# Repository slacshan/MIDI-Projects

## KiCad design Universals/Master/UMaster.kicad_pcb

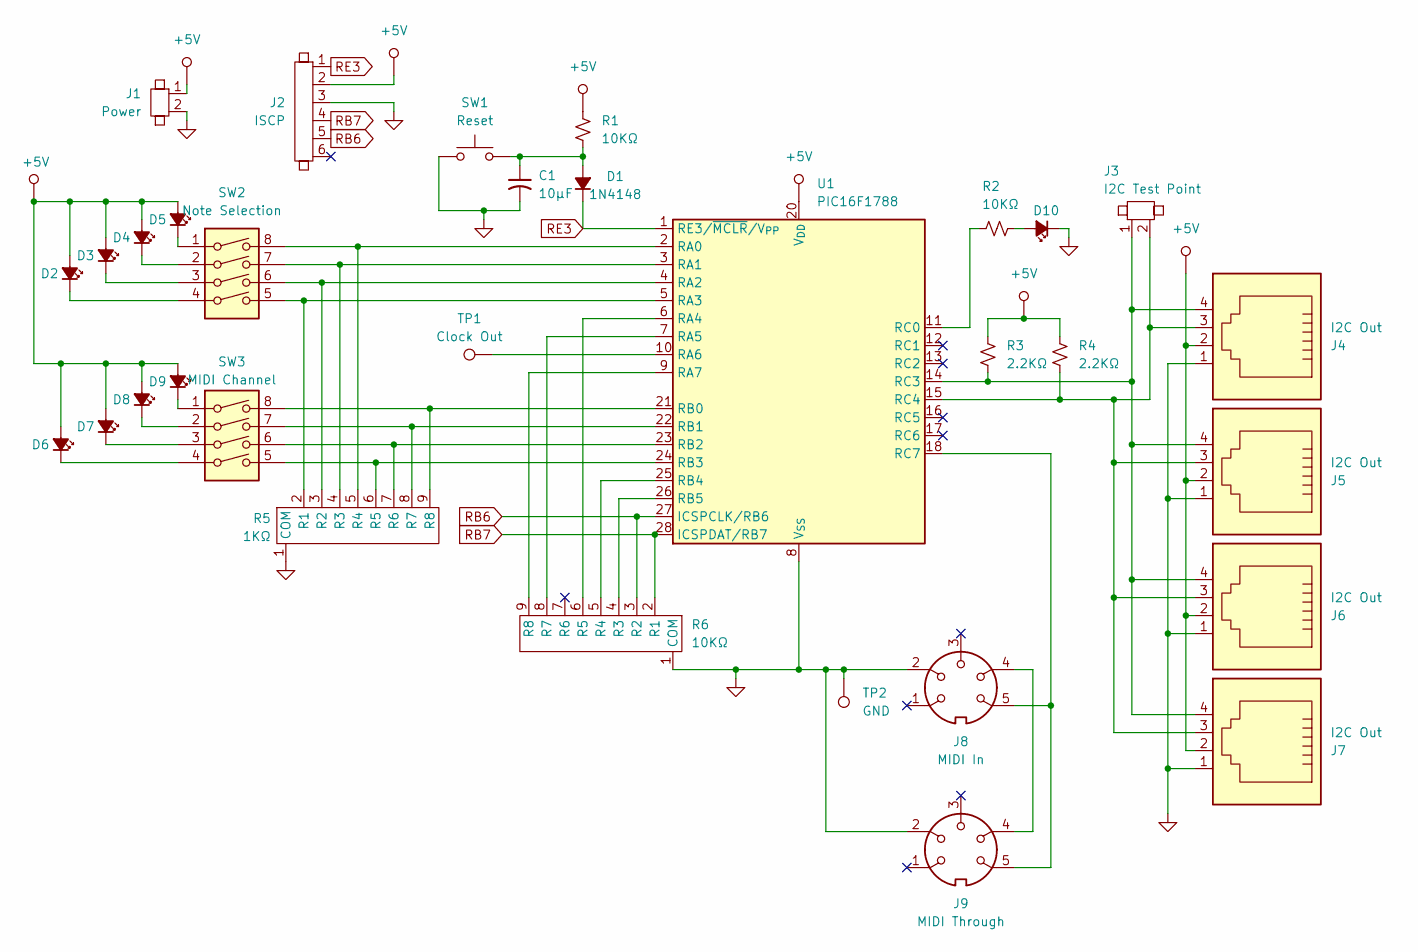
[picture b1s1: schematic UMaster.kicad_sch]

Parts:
C1: 10µF; C_Radial_D6.3mm_H11.0mm_P2.50mm
D1: 1N4148; D_0805
D2, D3, D4, D5, D6, D7, D8, D9, D10: LED_Small_Filled; D_0805
J1: Power; 2PinMolex
J2: ISCP; 1X6_100mil_Header
J3: I2C Test Point; 1X2_100mil_Header
J4, J5, J6, J7: I2C Out; RJ11
J8: MIDI In; DIN-5PIN_MIDI
J9: MIDI Through; DIN-5PIN_MIDI
R1, R2: 10KΩ; C_0805
R3, R4: 2.2KΩ; C_0805
R5: 1KΩ; 1x9_100mil_Header
R6: 10KΩ; 1x9_100mil_Header
SW1: Reset; SW_PUSH_6mm
SW2: Note Selection; DIP-8_W7.62mm
SW3: MIDI Channel; DIP-8_W7.62mm
TP1: Clock Out; 1X1_100mil_Header
TP2: GND; 1X1_100mil_Header
U1: PIC16F1788; QFN-28-1EP_6x6mm_P0.65mm_EP4.25x4.25mm

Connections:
GND: C1.2, D10.1 (K), J1.2, J2.3, J4.1, J5.1, J6.1, J7.1, J8.2, J9.2, R5.1 (COM), R6.1 (COM), SW1.1, TP2.1, U1.8 (V_{SS}), U1.19 (V_{SS})
unnamed: C1.1, D1.2 (A), R1.2, SW1.2
unnamed: D2.1 (K), SW2.4
unnamed: D3.1 (K), SW2.3
unnamed: D4.1 (K), SW2.2
unnamed: D5.1 (K), SW2.1
unnamed: D6.1 (K), SW3.4
unnamed: D7.1 (K), SW3.3
unnamed: D8.1 (K), SW3.2
unnamed: D9.1 (K), SW3.1
unnamed: D10.2 (A), R2.2
unnamed: J8.4, J9.4
unnamed: R5.2 (R1), SW2.5, U1.5 (RA3)
unnamed: R5.3 (R2), SW2.6, U1.4 (RA2)
unnamed: R5.4 (R3), SW2.7, U1.3 (RA1)
unnamed: R5.5 (R4), SW2.8, U1.2 (RA0)
unnamed: R5.6 (R5), SW3.5, U1.24 (RB3)
unnamed: R5.7 (R6), SW3.6, U1.23 (RB2)
unnamed: R5.8 (R7), SW3.7, U1.22 (RB1)
unnamed: R5.9 (R8), SW3.8, U1.21 (RB0)
unnamed: R6.4 (R3), U1.26 (RB5)
unnamed: R6.5 (R4), U1.25 (RB4)
unnamed: R6.6 (R5), U1.6 (RA4)
unnamed: R6.8 (R7), U1.7 (RA5)
unnamed: R6.9 (R8), U1.9 (RA7)
unnamed: TP1.1, U1.10 (RA6)
unnamed: R2.1, U1.11 (RC0)
unnamed: J3.1, J4.4, J5.4, J6.4, J7.4, R3.2, U1.14 (RC3)
unnamed: J3.2, J4.3, J5.3, J6.3, J7.3, R4.2, U1.15 (RC4)
unnamed: J8.5, J9.5, U1.18 (RC7)
RB6: J2.5, R6.3 (R2), U1.27 (ICSPCLK/RB6)
RB7: J2.4, R6.2 (R1), U1.28 (ICSPDAT/RB7)
RE3: D1.1 (K), J2.1, U1.1 (RE3/~MCLR/V_{PP})

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
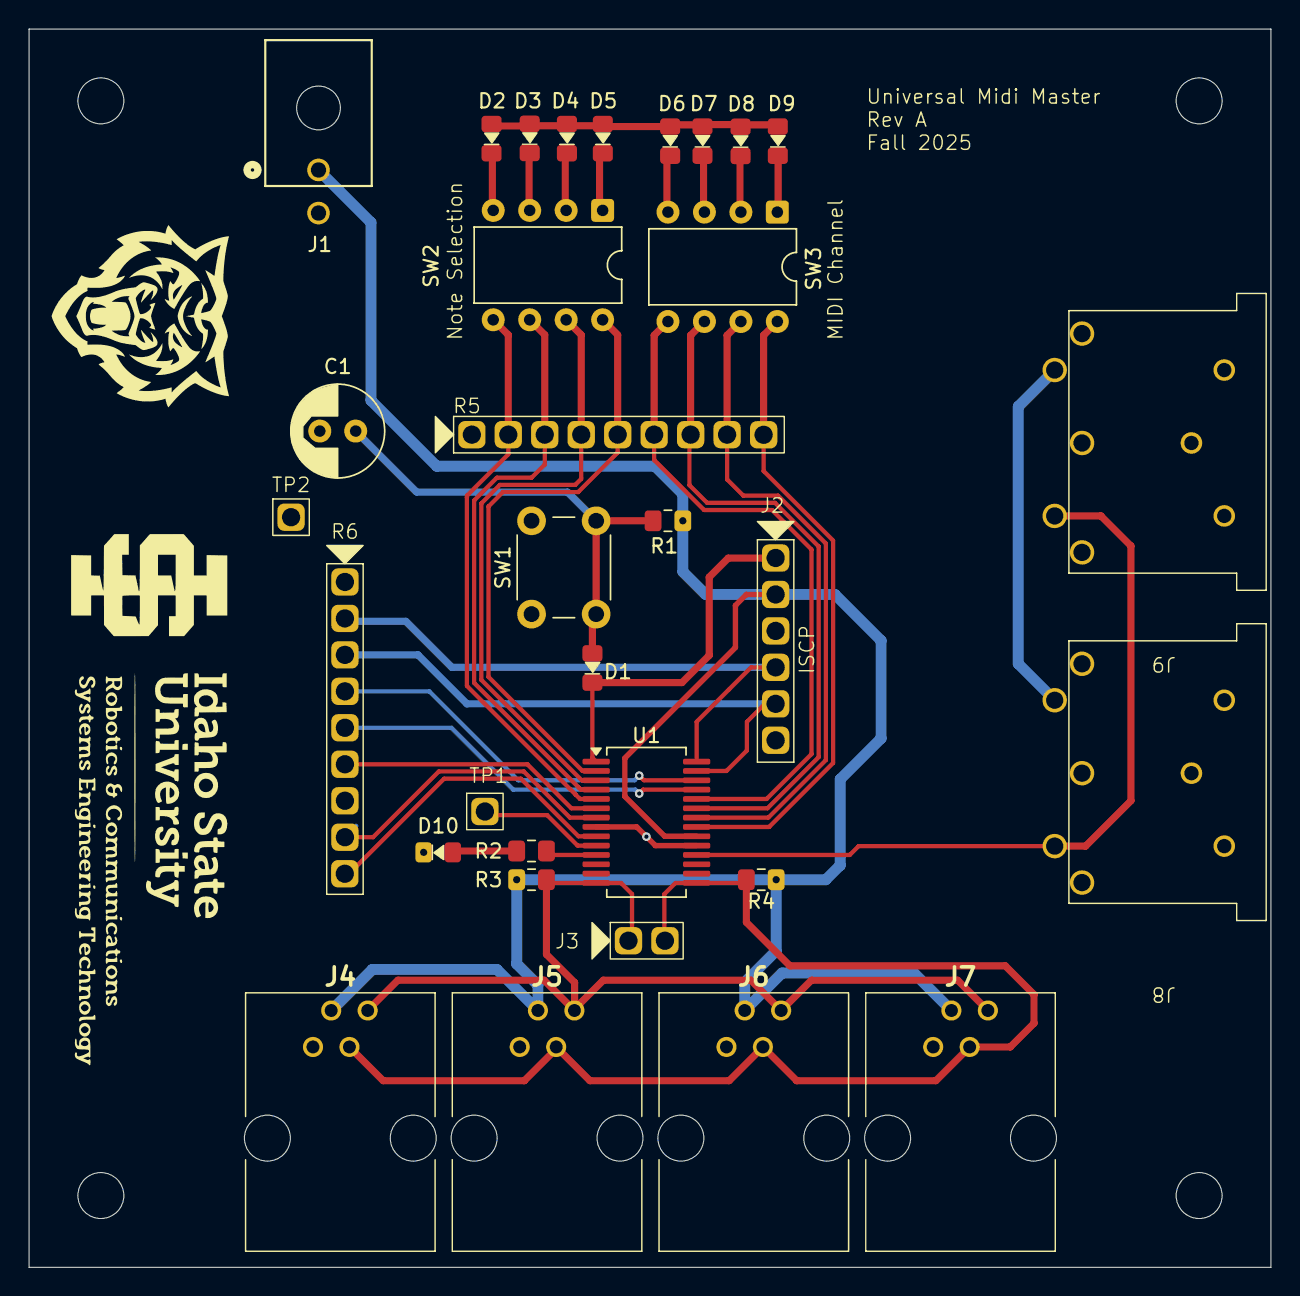
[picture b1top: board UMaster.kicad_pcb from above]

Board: 2 copper layers, 86.5 x 86.2 mm, 32 parts (0 on the bottom side), 35 nets.

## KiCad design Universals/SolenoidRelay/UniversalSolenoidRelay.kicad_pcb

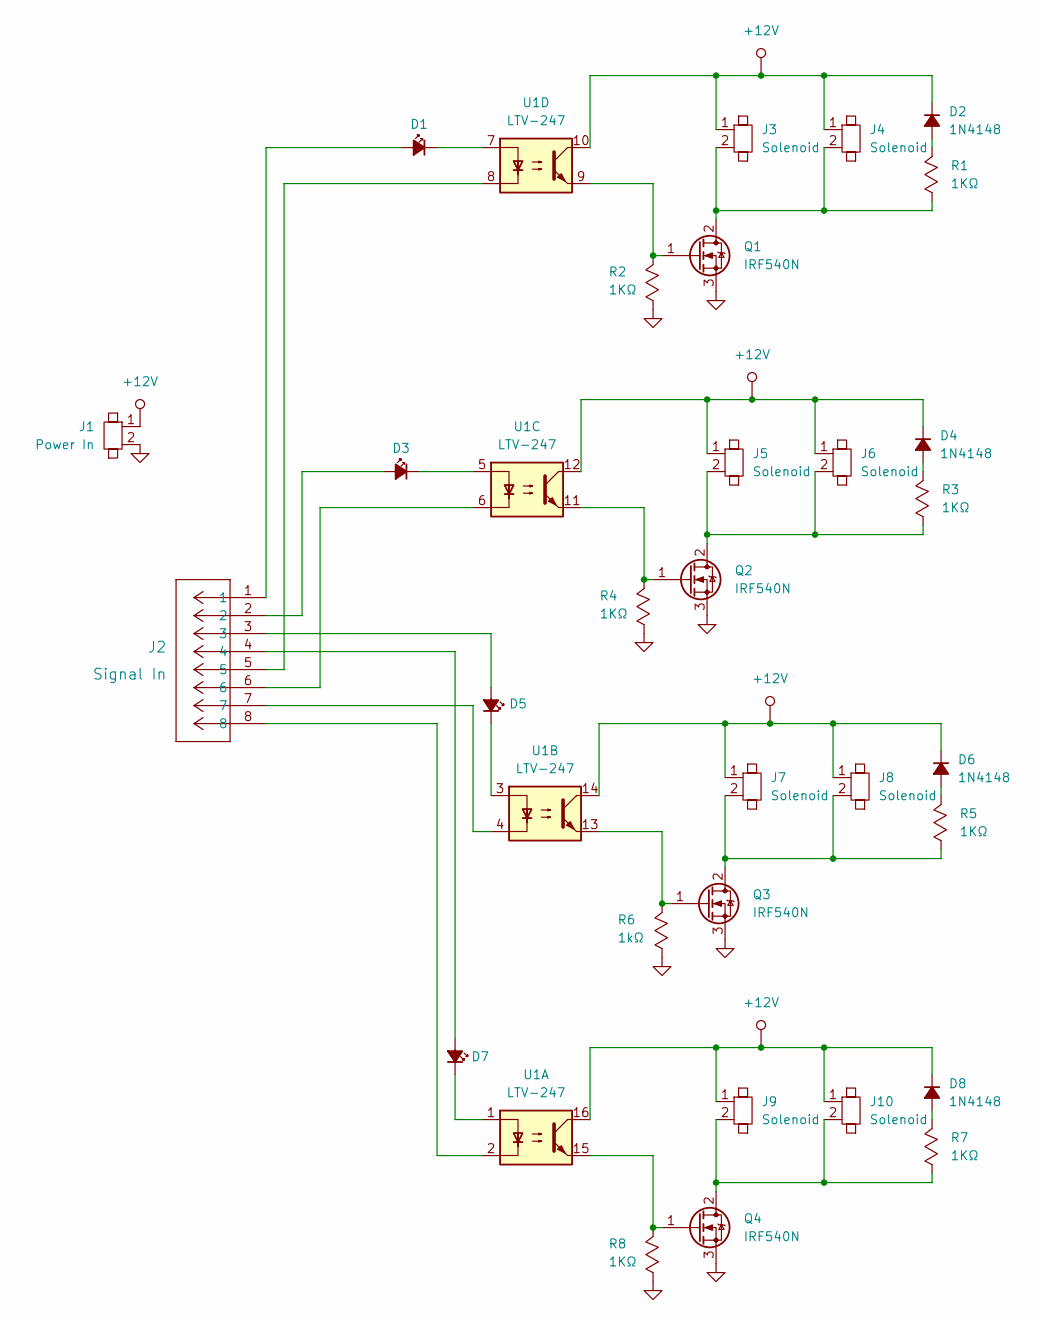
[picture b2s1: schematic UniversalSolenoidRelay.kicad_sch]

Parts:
D1, D3, D5, D7: LED; D_0805
D2, D4, D6, D8: 1N4148; D_0805
J1: Power In; 2PinMolex
J2: Signal In; 8PinMolex_3.00mmPitch
J3, J4, J5, J6, J7, J8, J9, J10: Solenoid; 2PinMolex
Q1, Q2, Q3, Q4: IRF540N; TO-220-3_Vertical
R1, R2, R3, R4, R5, R7, R8: 1KΩ; C_0805
R6: 1kΩ; C_0805
U1: LTV-247; SOP-16_4.4x10.4mm_P1.27mm

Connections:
GND: J1.2, Q1.3 (S), Q2.3 (S), Q3.3 (S), Q4.3 (S), R2.1, R4.1, R6.1, R8.1
unnamed: D1.2 (A), J2.1
unnamed: D1.1 (K), U1.7
unnamed: D2.2 (A), R1.2
unnamed: D3.2 (A), J2.2
unnamed: D3.1 (K), U1.5
unnamed: D4.2 (A), R3.2
unnamed: D5.2 (A), J2.3
unnamed: D5.1 (K), U1.3
unnamed: D6.2 (A), R5.2
unnamed: D7.2 (A), J2.4
unnamed: D7.1 (K), U1.1
unnamed: D8.2 (A), R7.2
unnamed: D2.1 (K), D4.1 (K), D6.1 (K), D8.1 (K), J1.1, J3.1, J4.1, J5.1, J6.1, J7.1, J8.1, J9.1, J10.1, U1.10, U1.12, U1.14, U1.16
unnamed: J2.5, U1.8
unnamed: J2.6, U1.6
unnamed: J2.7, U1.4
unnamed: J2.8, U1.2
unnamed: J3.2, J4.2, Q1.2 (D), R1.1
unnamed: Q1.1 (G), R2.2, U1.9
unnamed: J5.2, J6.2, Q2.2 (D), R3.1
unnamed: Q2.1 (G), R4.2, U1.11
unnamed: J7.2, J8.2, Q3.2 (D), R5.1
unnamed: Q3.1 (G), R6.2, U1.13
unnamed: J9.2, J10.2, Q4.2 (D), R7.1
unnamed: Q4.1 (G), R8.2, U1.15

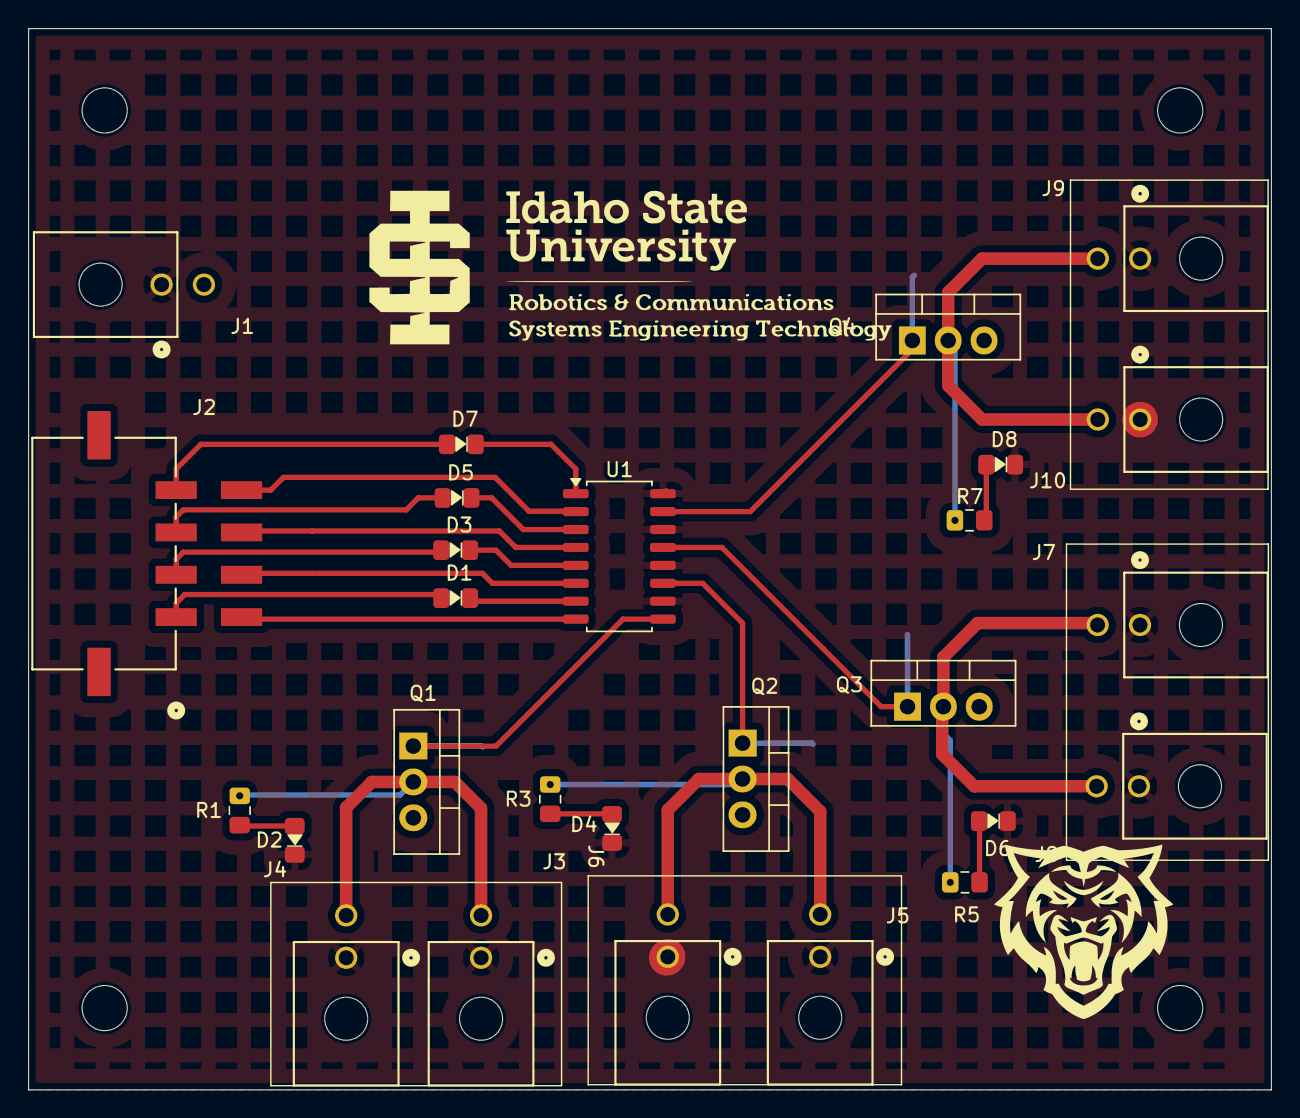
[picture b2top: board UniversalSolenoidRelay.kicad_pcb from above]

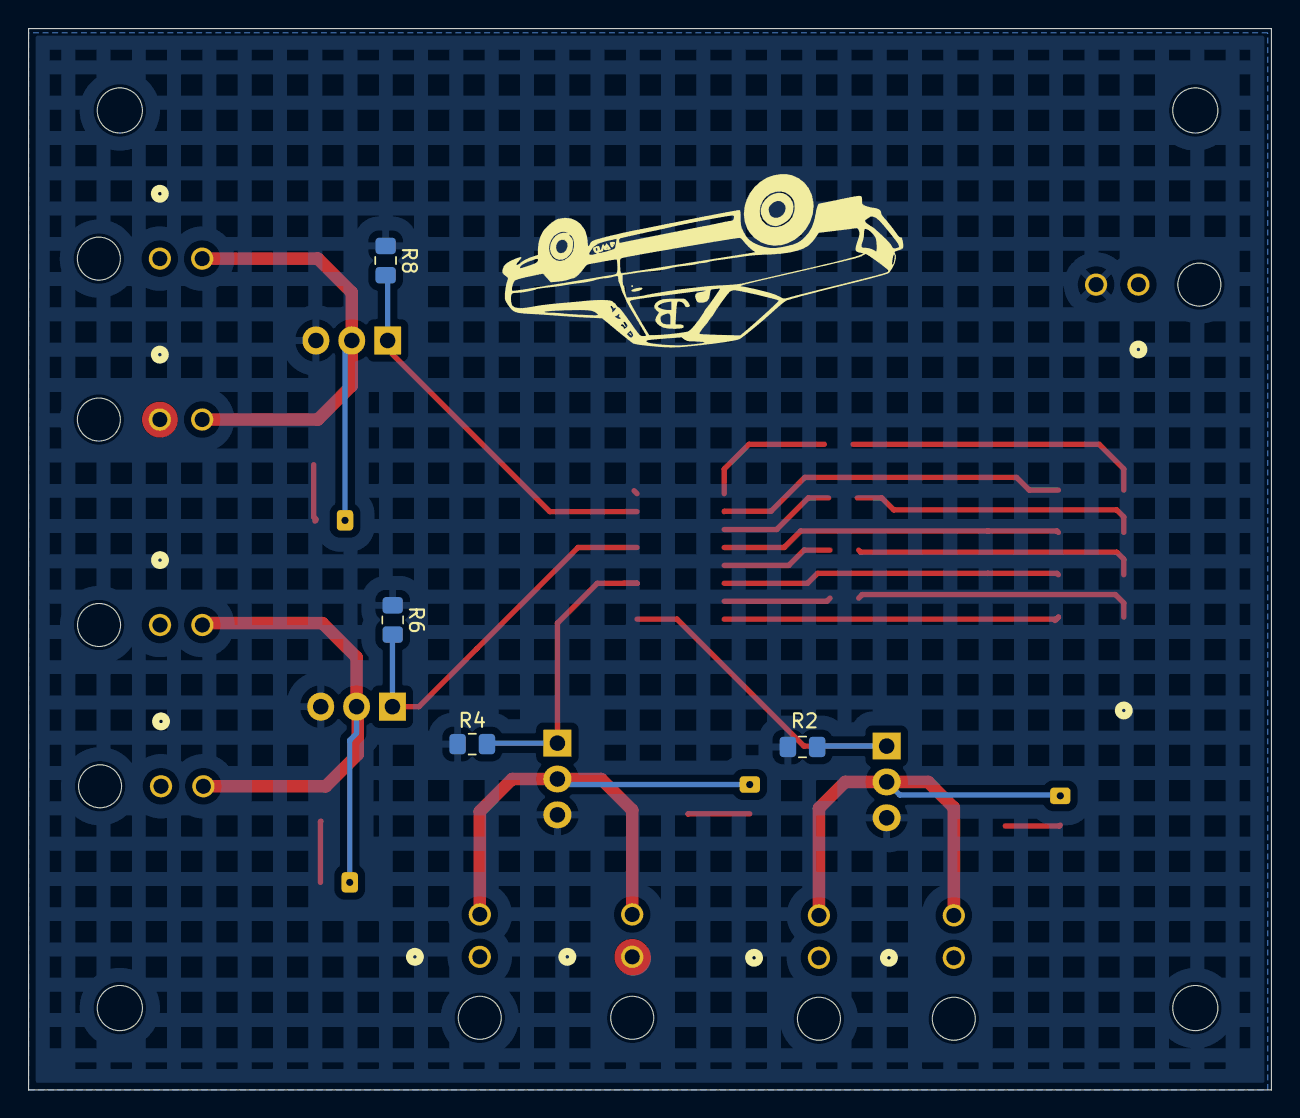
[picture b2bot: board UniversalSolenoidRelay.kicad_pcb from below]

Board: 2 copper layers, 88.1 x 75.2 mm, 31 parts (4 on the bottom side), 26 nets.

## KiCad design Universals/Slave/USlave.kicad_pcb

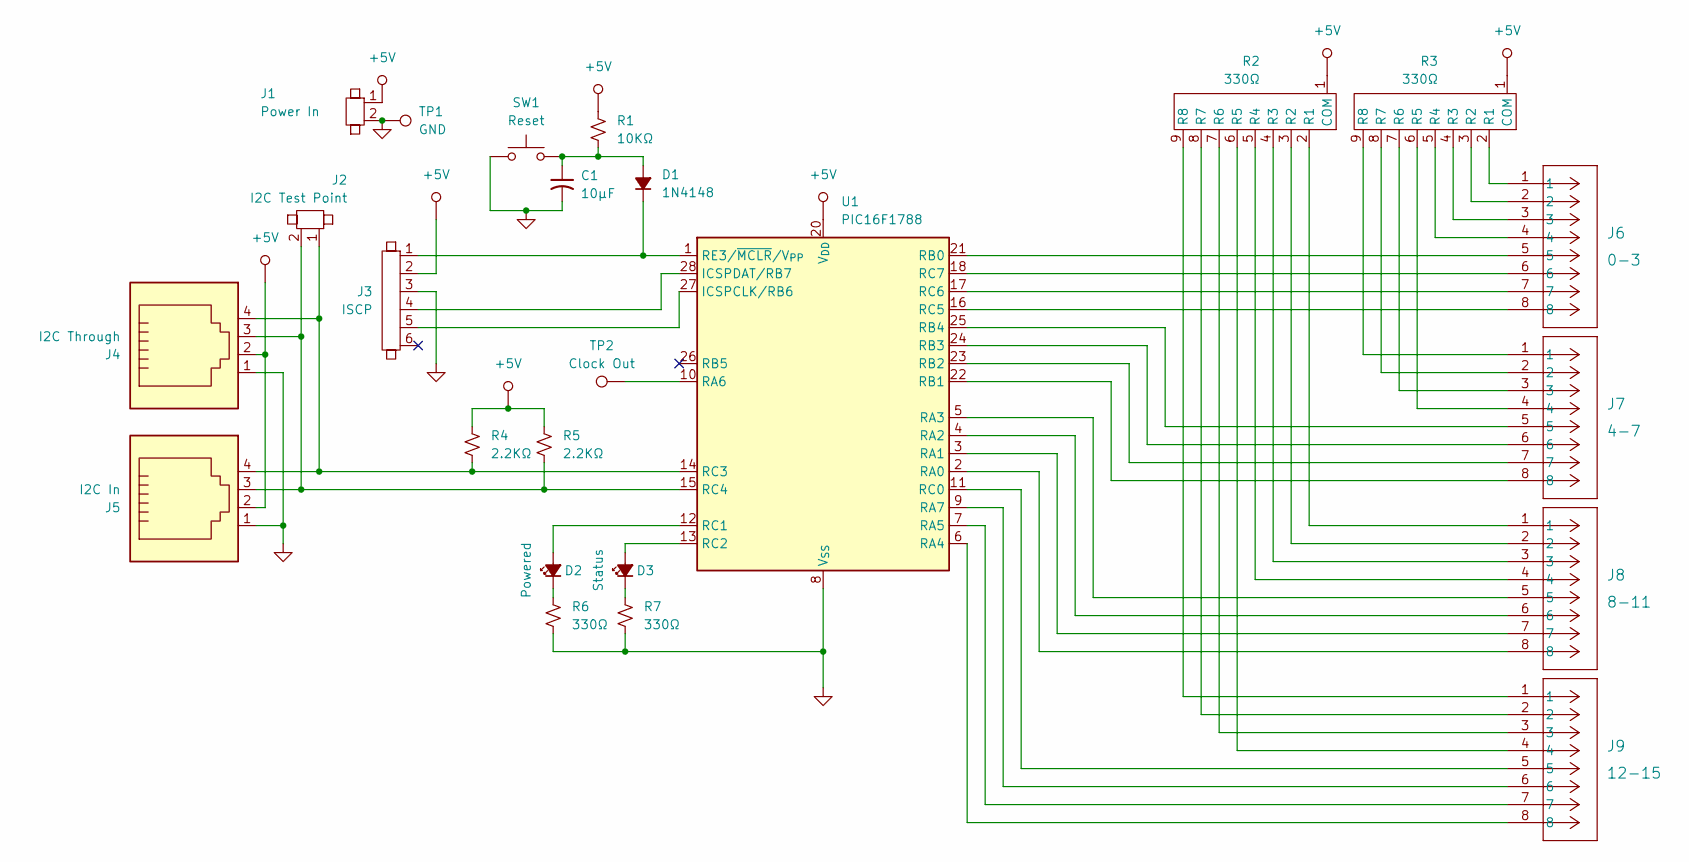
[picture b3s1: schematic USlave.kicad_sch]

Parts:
C1: 10µF; C_Radial_D6.3mm_H11.0mm_P2.50mm
D1: 1N4148; D_0805
D2: Powered; D_0805
D3: Status; D_0805
J1: Power In; 2PinMolex
J2: I2C Test Point; 1X2_100mil_Header
J3: ISCP; 1X6_100mil_Header
J4: I2C Through; RJ11
J5: I2C In; RJ11
J6: 0-3; 8PinMolex_3.00mmPitch
J7: 4-7; 8PinMolex_3.00mmPitch
J8: 8-11; 8PinMolex_3.00mmPitch
J9: 12-15; 8PinMolex_3.00mmPitch
R1: 10KΩ; C_0805
R2, R3: 330Ω; 1x9_100mil_Header
R4, R5: 2.2KΩ; C_0805
R6, R7: 330Ω; C_0805
SW1: Reset; SW_TH_Tactile_Omron_B3F-100x
TP1: GND; 1X1_100mil_Header
TP2: Clock Out; 1X1_100mil_Header
U1: PIC16F1788; QFN-28-1EP_6x6mm_P0.65mm_EP4.25x4.25mm

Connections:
GND: C1.2, J1.2, J3.3, J4.1, J5.1, R6.2, R7.2, SW1.1, TP1.1, U1.8 (V_{SS}), U1.19 (V_{SS})
unnamed: C1.1, D1.2 (A), R1.2, SW1.2
unnamed: D1.1 (K), J3.1, U1.1 (RE3/~MCLR/V_{PP})
unnamed: D2.2 (A), U1.12 (RC1)
unnamed: D2.1 (K), R6.1
unnamed: D3.2 (A), U1.13 (RC2)
unnamed: D3.1 (K), R7.1
unnamed: J8.1, R2.2 (R1)
unnamed: J8.2, R2.3 (R2)
unnamed: J8.3, R2.4 (R3)
unnamed: J8.4, R2.5 (R4)
unnamed: J9.4, R2.6 (R5)
unnamed: J9.3, R2.7 (R6)
unnamed: J9.2, R2.8 (R7)
unnamed: J9.1, R2.9 (R8)
unnamed: J6.1, R3.2 (R1)
unnamed: J6.2, R3.3 (R2)
unnamed: J6.3, R3.4 (R3)
unnamed: J6.4, R3.5 (R4)
unnamed: J7.4, R3.6 (R5)
unnamed: J7.3, R3.7 (R6)
unnamed: J7.2, R3.8 (R7)
unnamed: J7.1, R3.9 (R8)
unnamed: J3.5, U1.27 (ICSPCLK/RB6)
unnamed: J3.4, U1.28 (ICSPDAT/RB7)
unnamed: J8.8, U1.2 (RA0)
unnamed: J8.7, U1.3 (RA1)
unnamed: J8.6, U1.4 (RA2)
unnamed: J8.5, U1.5 (RA3)
unnamed: J9.8, U1.6 (RA4)
unnamed: J9.7, U1.7 (RA5)
unnamed: TP2.1, U1.10 (RA6)
unnamed: J9.6, U1.9 (RA7)
unnamed: J6.5, U1.21 (RB0)
unnamed: J7.8, U1.22 (RB1)
unnamed: J7.7, U1.23 (RB2)
unnamed: J7.6, U1.24 (RB3)
unnamed: J7.5, U1.25 (RB4)
unnamed: J9.5, U1.11 (RC0)
unnamed: J2.1, J4.4, J5.4, R4.2, U1.14 (RC3)
unnamed: J2.2, J4.3, J5.3, R5.2, U1.15 (RC4)
unnamed: J6.8, U1.16 (RC5)
unnamed: J6.7, U1.17 (RC6)
unnamed: J6.6, U1.18 (RC7)

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
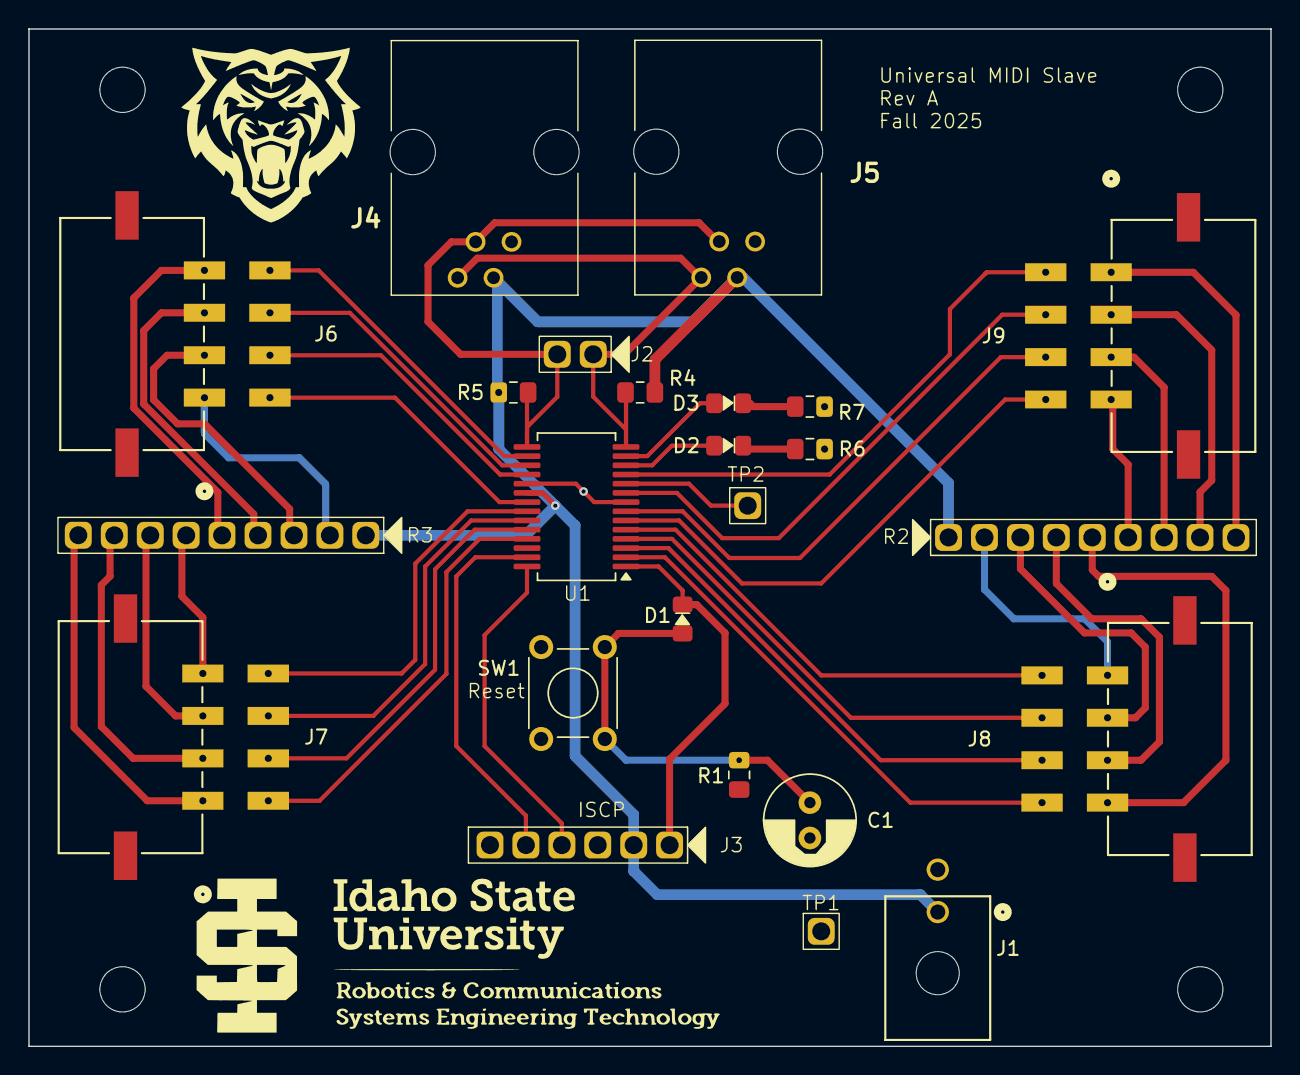
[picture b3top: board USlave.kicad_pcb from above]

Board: 2 copper layers, 87.8 x 71.9 mm, 24 parts (0 on the bottom side), 45 nets.

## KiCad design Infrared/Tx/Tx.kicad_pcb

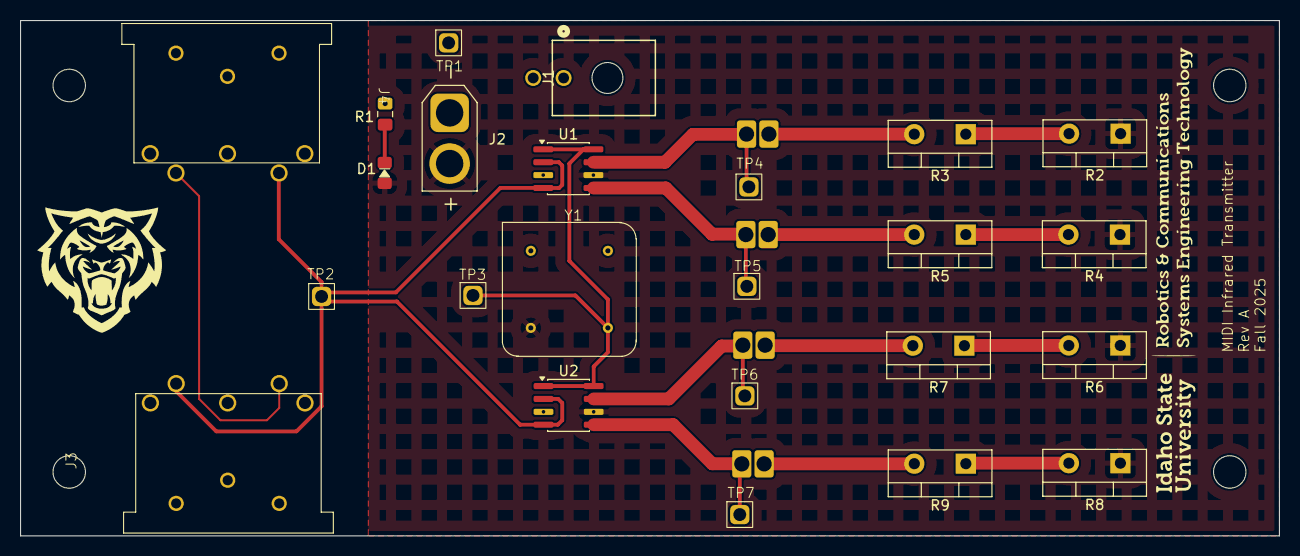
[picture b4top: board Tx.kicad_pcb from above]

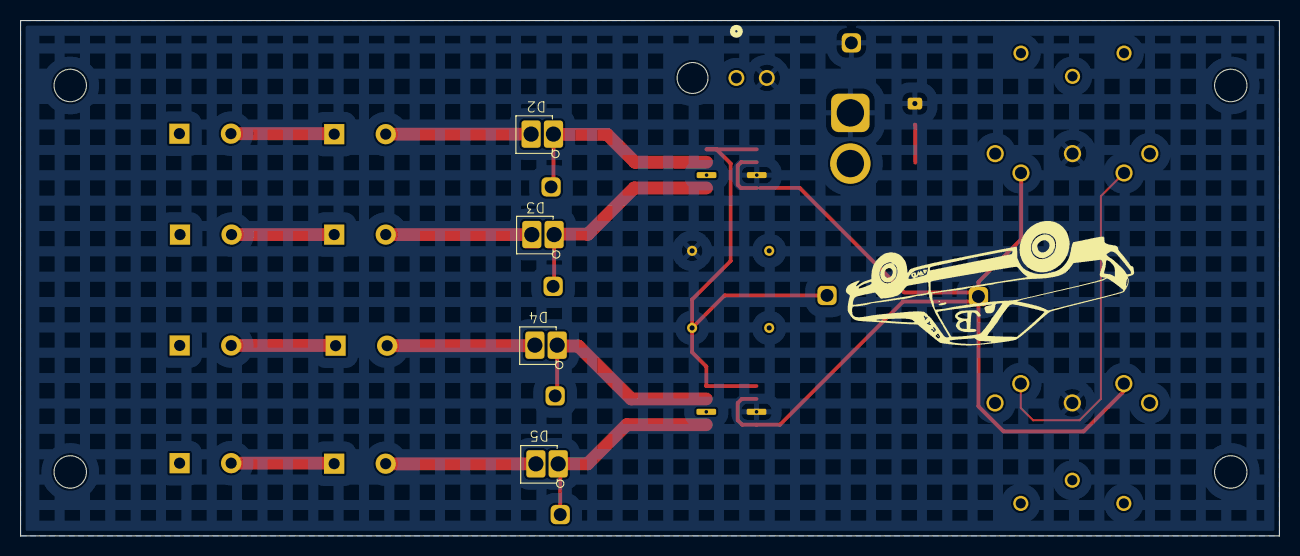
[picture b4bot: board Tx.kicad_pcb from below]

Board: 2 copper layers, 124.1 x 50.8 mm, 28 parts (4 on the bottom side), 18 nets.

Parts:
D1: LED_Filled; D_0805
D2, D3, D4, D5: D_Filled; Fat_2Pin_D
J1: FanPower; 2PinMolex
J2: Power In; AMASS_XT30U-F_1x02_P5.0mm_Vertical
J3: MIDI Thr; DIN-5PIN_MIDI
J4: MIDI in; DIN-5PIN_MIDI
R1: 330Ω; C_0805
R2, R3, R4, R5, R6, R7, R8, R9: 2Ω; TO-220-2_Vertical
TP1: GND; 1X1_100mil_Header
TP2: MIDI_Input; 1X1_100mil_Header
TP3: 1MHzTP; 1X1_100mil_Header
TP4: IR1; 1X1_100mil_Header
TP5: IR2; 1X1_100mil_Header
TP6: IR3; 1X1_100mil_Header
TP7: IR4; 1X1_100mil_Header
U1, U2: MCP14E3; SOIC-8_3.9x4.9mm_P1.27mm
Y1: 1MHz; 300x300Mil_4Pin_Y

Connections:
GND: J1.2, J2.1, J3.2, J4.2, R1.2, TP1.1, U1.3 (GND), U2.3 (GND), Y1.4
unnamed: D1.1 (K), R1.1
unnamed: D2.1 (A), R3.2
unnamed: D2.2 (K), TP4.1, U1.7 (~OUTA)
unnamed: D3.1 (A), R5.2
unnamed: D3.2 (K), TP5.1, U1.5 (~OUTB)
unnamed: D4.1 (A), R7.2
unnamed: D4.2 (K), TP6.1, U2.7 (~OUTA)
unnamed: D5.1 (A), R9.2
unnamed: D5.2 (K), TP7.1, U2.5 (~OUTB)
unnamed: J3.4, J4.4
unnamed: R2.2, R3.1
unnamed: R4.2, R5.1
unnamed: R6.2, R7.1
unnamed: R8.2, R9.1
unnamed: TP3.1, U1.1 (ENA), U1.8 (ENB), U2.1 (ENA), U2.8 (ENB), Y1.5
unnamed: J3.5, J4.5, TP2.1, U1.2 (INA), U1.4 (INB), U2.2 (INA), U2.4 (INB)
unnamed: D1.2 (A), J2.2, R2.1, R4.1, R6.1, R8.1, U1.6 (VCC), U2.6 (VCC), Y1.8

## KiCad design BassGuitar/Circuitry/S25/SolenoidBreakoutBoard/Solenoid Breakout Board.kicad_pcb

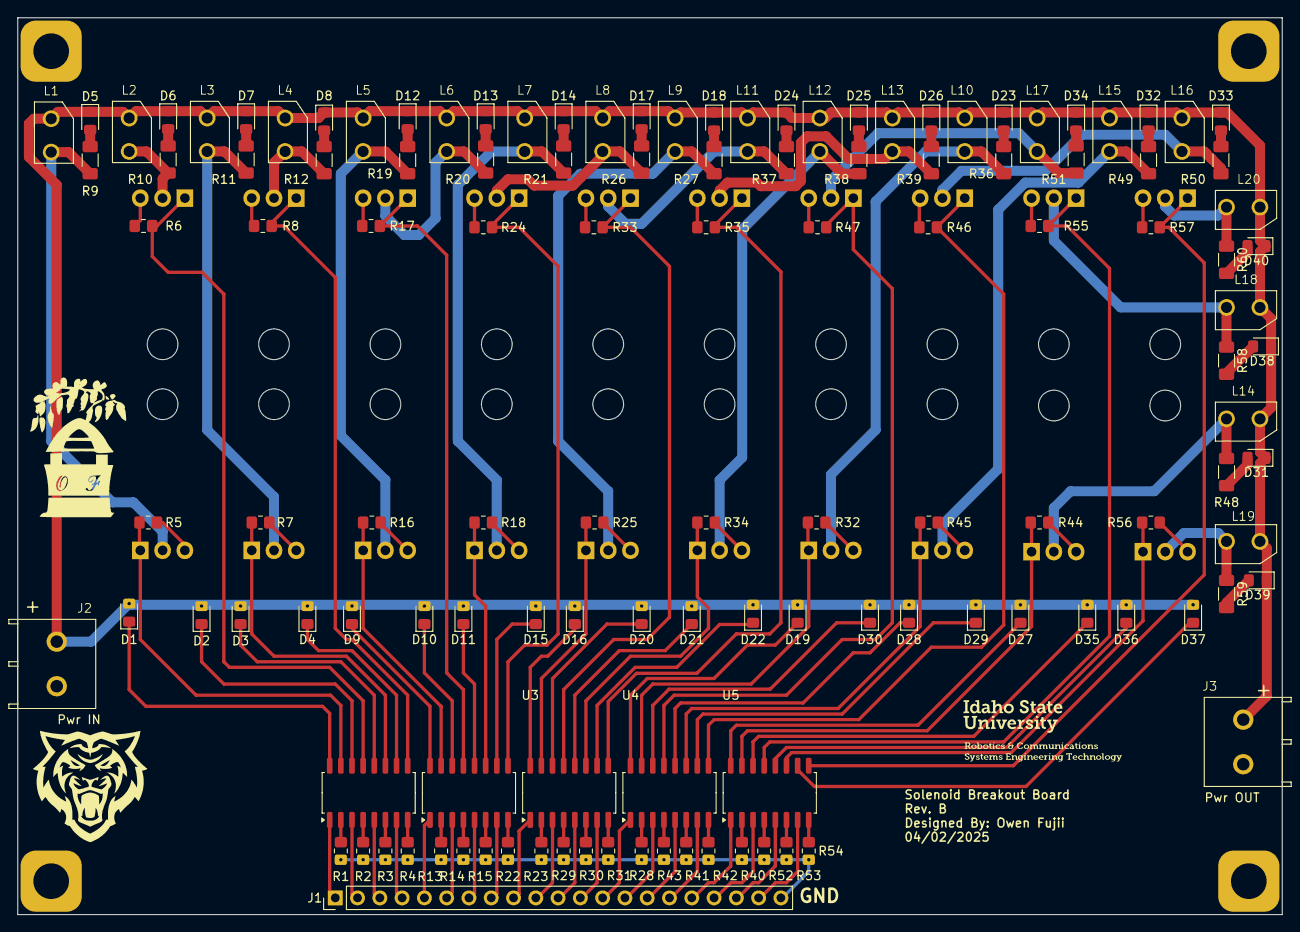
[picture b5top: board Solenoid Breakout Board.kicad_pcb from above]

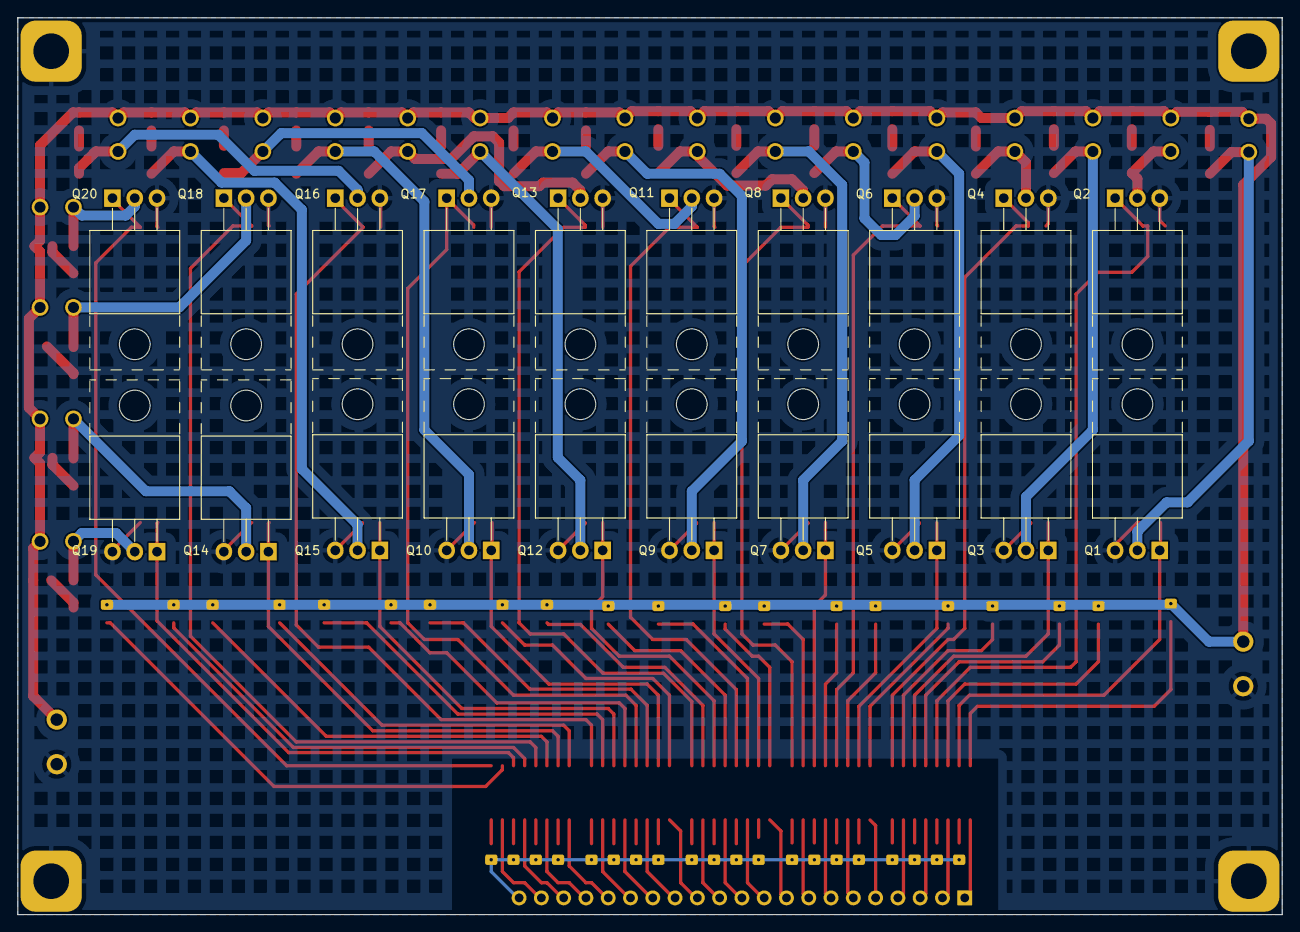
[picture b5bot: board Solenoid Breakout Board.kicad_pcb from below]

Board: 2 copper layers, 144.1 x 102.2 mm, 148 parts (20 on the bottom side), 123 nets.

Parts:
D1, D2, D3, D4, D9, D10, D11, D15, D16, D19, D20, D21, D22, D27, D28, D29, D30, D35, D36, D37: LED; LED_0805_2012Metric_Pad1.15x1.40mm_HandSolder
D5, D6, D7, D8, D12, D13, D14, D17, D18, D23, D24, D25, D26, D31, D32, D33, D34, D38, D39, D40: 1N4148; LED_0805_2012Metric_Pad1.15x1.40mm_HandSolder
J1: Solenoid In; PinHeader_1x21_P2.54mm_Vertical
J2: Pwr IN; Two_Pin_Screw_Terminal
J3: Pwr OUT; Two_Pin_Screw_Terminal
L1, L2, L3, L4, L5, L6, L7, L8, L9, L10, L11, L12, L13, L14, L15, L16, L17, L18, L19, L20: Solenoid; Small Expanded TH
Q1, Q2, Q3, Q4, Q5, Q6, Q7, Q8, Q9, Q10, Q11, Q12, Q13, Q14, Q15, Q16, Q17, Q18, Q19, Q20: IRF540N; TO-220-3_Horizontal_TabUp
R1, R2, R3, R4, R5, R6, R7, R8, R13, R14, R15, R16, R17, R18, R22, R23, R24, R25, R28, R29, R30, R31, R32, R33, R34, R35, R40, R41, R42, R43, R44, R45, R46, R47, R52, R53, R54, R55, R56, R57: 1kΩ; R_0805_2012Metric_Pad1.20x1.40mm_HandSolder
R9, R10, R11, R12, R19, R20, R21, R26, R27, R36, R37, R38, R39, R48, R49, R50, R51, R58, R59, R60: 1kΩ-P; R_1206_3216Metric_Pad1.30x1.75mm_HandSolder
U1, U2, U3, U4, U5: LTV-247; SOP-16_4.4x10.4mm_P1.27mm

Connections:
+12v: D1.2 (A), D2.2 (A), D3.2 (A), D4.2 (A), D5.1 (K), D6.1 (K), D7.1 (K), D8.1 (K), D9.2 (A), D10.2 (A), D11.2 (A), D12.1 (K), D13.1 (K), D14.1 (K), D15.2 (A), D16.2 (A), D17.1 (K), D18.1 (K), D19.2 (A), D20.2 (A), D21.2 (A), D22.2 (A), D23.1 (K), D24.1 (K), D25.1 (K), D26.1 (K), D27.2 (A), D28.2 (A), D29.2 (A), D30.2 (A), D31.1 (K), D32.1 (K), D33.1 (K), D34.1 (K), D35.2 (A), D36.2 (A), D37.2 (A), D38.1 (K), D39.1 (K), D40.1 (K), J2.1, J3.2, L1.1, L2.1, L3.1, L4.1, L5.1, L6.1, L7.1, L8.1, L9.1, L10.1, L11.1, L12.1, L13.1, L14.1, L15.1, L16.1, L17.1, L18.1, L19.1, L20.1
A1: J1.5, U2.1
A2: J1.17, U5.1
A#1: J1.6, U2.3
A#2: J1.18, U5.3
B1: J1.7, U2.5
B2: J1.19, U5.5
C2: J1.8, U2.7
C3: J1.20, U5.7
C#2: J1.9, U3.1
Chassis_GND: J2.2, J3.1, Q1.3 (S), Q2.3 (S), Q3.3 (S), Q4.3 (S), Q5.3 (S), Q6.3 (S), Q7.3 (S), Q8.3 (S), Q9.3 (S), Q10.3 (S), Q11.3 (S), Q12.3 (S), Q13.3 (S), Q14.3 (S), Q15.3 (S), Q16.3 (S), Q17.3 (S), Q18.3 (S), Q19.3 (S), Q20.3 (S), R5.1, R6.1, R7.1, R8.1, R16.1, R17.1, R18.1, R24.1, R25.1, R32.1, R33.1, R34.1, R35.1, R44.1, R45.1, R46.1, R47.1, R55.1, R56.1, R57.1
D2: J1.10, U3.3
D#2: J1.11, U3.5
E2: J1.12, U3.7
F1: J1.1, U1.1
F2: J1.13, U4.1
F#1: J1.2, U1.3
F#2: J1.14, U4.3
G1: J1.3, U1.5
G2: J1.15, U4.5
G#1: J1.4, U1.7
G#2: J1.16, U4.7
GND: J1.21, R1.1, R2.1, R3.1, R4.1, R13.1, R14.1, R15.1, R22.1, R23.1, R28.1, R29.1, R30.1, R31.1, R40.1, R41.1, R42.1, R43.1, R52.1, R53.1, R54.1
unnamed: D1.1 (K), U1.16
unnamed: D2.1 (K), U1.14
unnamed: D3.1 (K), U1.12
unnamed: D4.1 (K), U1.10
unnamed: D5.2 (A), R9.2
unnamed: D6.2 (A), R10.2
unnamed: D7.2 (A), R11.2
unnamed: D8.2 (A), R12.2
unnamed: D9.1 (K), U2.16
unnamed: D10.1 (K), U2.14
unnamed: D11.1 (K), U2.12
unnamed: D12.2 (A), R19.2
unnamed: D13.2 (A), R20.2
unnamed: D14.2 (A), R21.2
unnamed: D15.1 (K), U2.10
unnamed: D16.1 (K), U3.16
unnamed: D17.2 (A), R26.2
unnamed: D18.2 (A), R27.2
unnamed: D19.1 (K), U4.16
unnamed: D20.1 (K), U3.14
unnamed: D21.1 (K), U3.12
unnamed: D22.1 (K), U3.10
unnamed: D23.2 (A), R36.2
unnamed: D24.2 (A), R37.2
unnamed: D25.2 (A), R38.2
unnamed: D26.2 (A), R39.2
unnamed: D27.1 (K), U5.16
unnamed: D28.1 (K), U4.12
unnamed: D29.1 (K), U4.10
unnamed: D30.1 (K), U4.14
unnamed: D31.2 (A), R48.2
unnamed: D32.2 (A), R49.2
unnamed: D33.2 (A), R50.2
unnamed: D34.2 (A), R51.2
unnamed: D35.1 (K), U5.14
unnamed: D36.1 (K), U5.12
unnamed: D37.1 (K), U5.10
unnamed: D38.2 (A), R58.2
unnamed: D39.2 (A), R59.2
unnamed: D40.2 (A), R60.2
unnamed: L1.2, Q1.2 (D), R9.1
unnamed: Q1.1 (G), R5.2, U1.15
unnamed: L2.2, Q2.2 (D), R10.1
unnamed: Q2.1 (G), R6.2, U1.13
unnamed: L3.2, Q3.2 (D), R11.1
unnamed: Q3.1 (G), R7.2, U1.11
unnamed: L4.2, Q4.2 (D), R12.1
unnamed: Q4.1 (G), R8.2, U1.9
unnamed: L5.2, Q5.2 (D), R19.1
unnamed: Q5.1 (G), R16.2, U2.15
unnamed: L6.2, Q6.2 (D), R20.1
unnamed: Q6.1 (G), R17.2, U2.13
unnamed: L7.2, Q7.2 (D), R21.1
unnamed: Q7.1 (G), R18.2, U2.11
unnamed: L8.2, Q8.2 (D), R26.1
unnamed: Q8.1 (G), R24.2, U2.9
unnamed: L9.2, Q9.2 (D), R27.1
unnamed: Q9.1 (G), R25.2, U3.15
unnamed: L10.2, Q10.2 (D), R36.1
unnamed: Q10.1 (G), R32.2, U4.15
unnamed: L11.2, Q11.2 (D), R37.1
unnamed: Q11.1 (G), R33.2, U3.13
unnamed: L12.2, Q12.2 (D), R38.1
unnamed: Q12.1 (G), R34.2, U3.11
unnamed: L13.2, Q13.2 (D), R39.1
unnamed: Q13.1 (G), R35.2, U3.9
unnamed: L14.2, Q14.2 (D), R48.1
unnamed: Q14.1 (G), R44.2, U5.15
unnamed: L15.2, Q15.2 (D), R49.1
unnamed: Q15.1 (G), R45.2, U4.11
unnamed: L16.2, Q16.2 (D), R50.1
unnamed: Q16.1 (G), R46.2, U4.9
unnamed: L17.2, Q17.2 (D), R51.1
unnamed: Q17.1 (G), R47.2, U4.13
unnamed: L18.2, Q18.2 (D), R58.1
unnamed: Q18.1 (G), R55.2, U5.13
unnamed: L19.2, Q19.2 (D), R59.1
unnamed: Q19.1 (G), R56.2, U5.11
unnamed: L20.2, Q20.2 (D), R60.1
unnamed: Q20.1 (G), R57.2, U5.9
unnamed: R1.2, U1.2
unnamed: R2.2, U1.4
unnamed: R3.2, U1.6
unnamed: R4.2, U1.8
unnamed: R13.2, U2.2
unnamed: R14.2, U2.4
unnamed: R15.2, U2.6
unnamed: R22.2, U2.8
unnamed: R23.2, U3.2
unnamed: R28.2, U4.2
unnamed: R29.2, U3.4
unnamed: R30.2, U3.6
unnamed: R31.2, U3.8
unnamed: R40.2, U5.2
unnamed: R41.2, U4.6
unnamed: R42.2, U4.8
unnamed: R43.2, U4.4
unnamed: R52.2, U5.4
unnamed: R53.2, U5.6
unnamed: R54.2, U5.8
